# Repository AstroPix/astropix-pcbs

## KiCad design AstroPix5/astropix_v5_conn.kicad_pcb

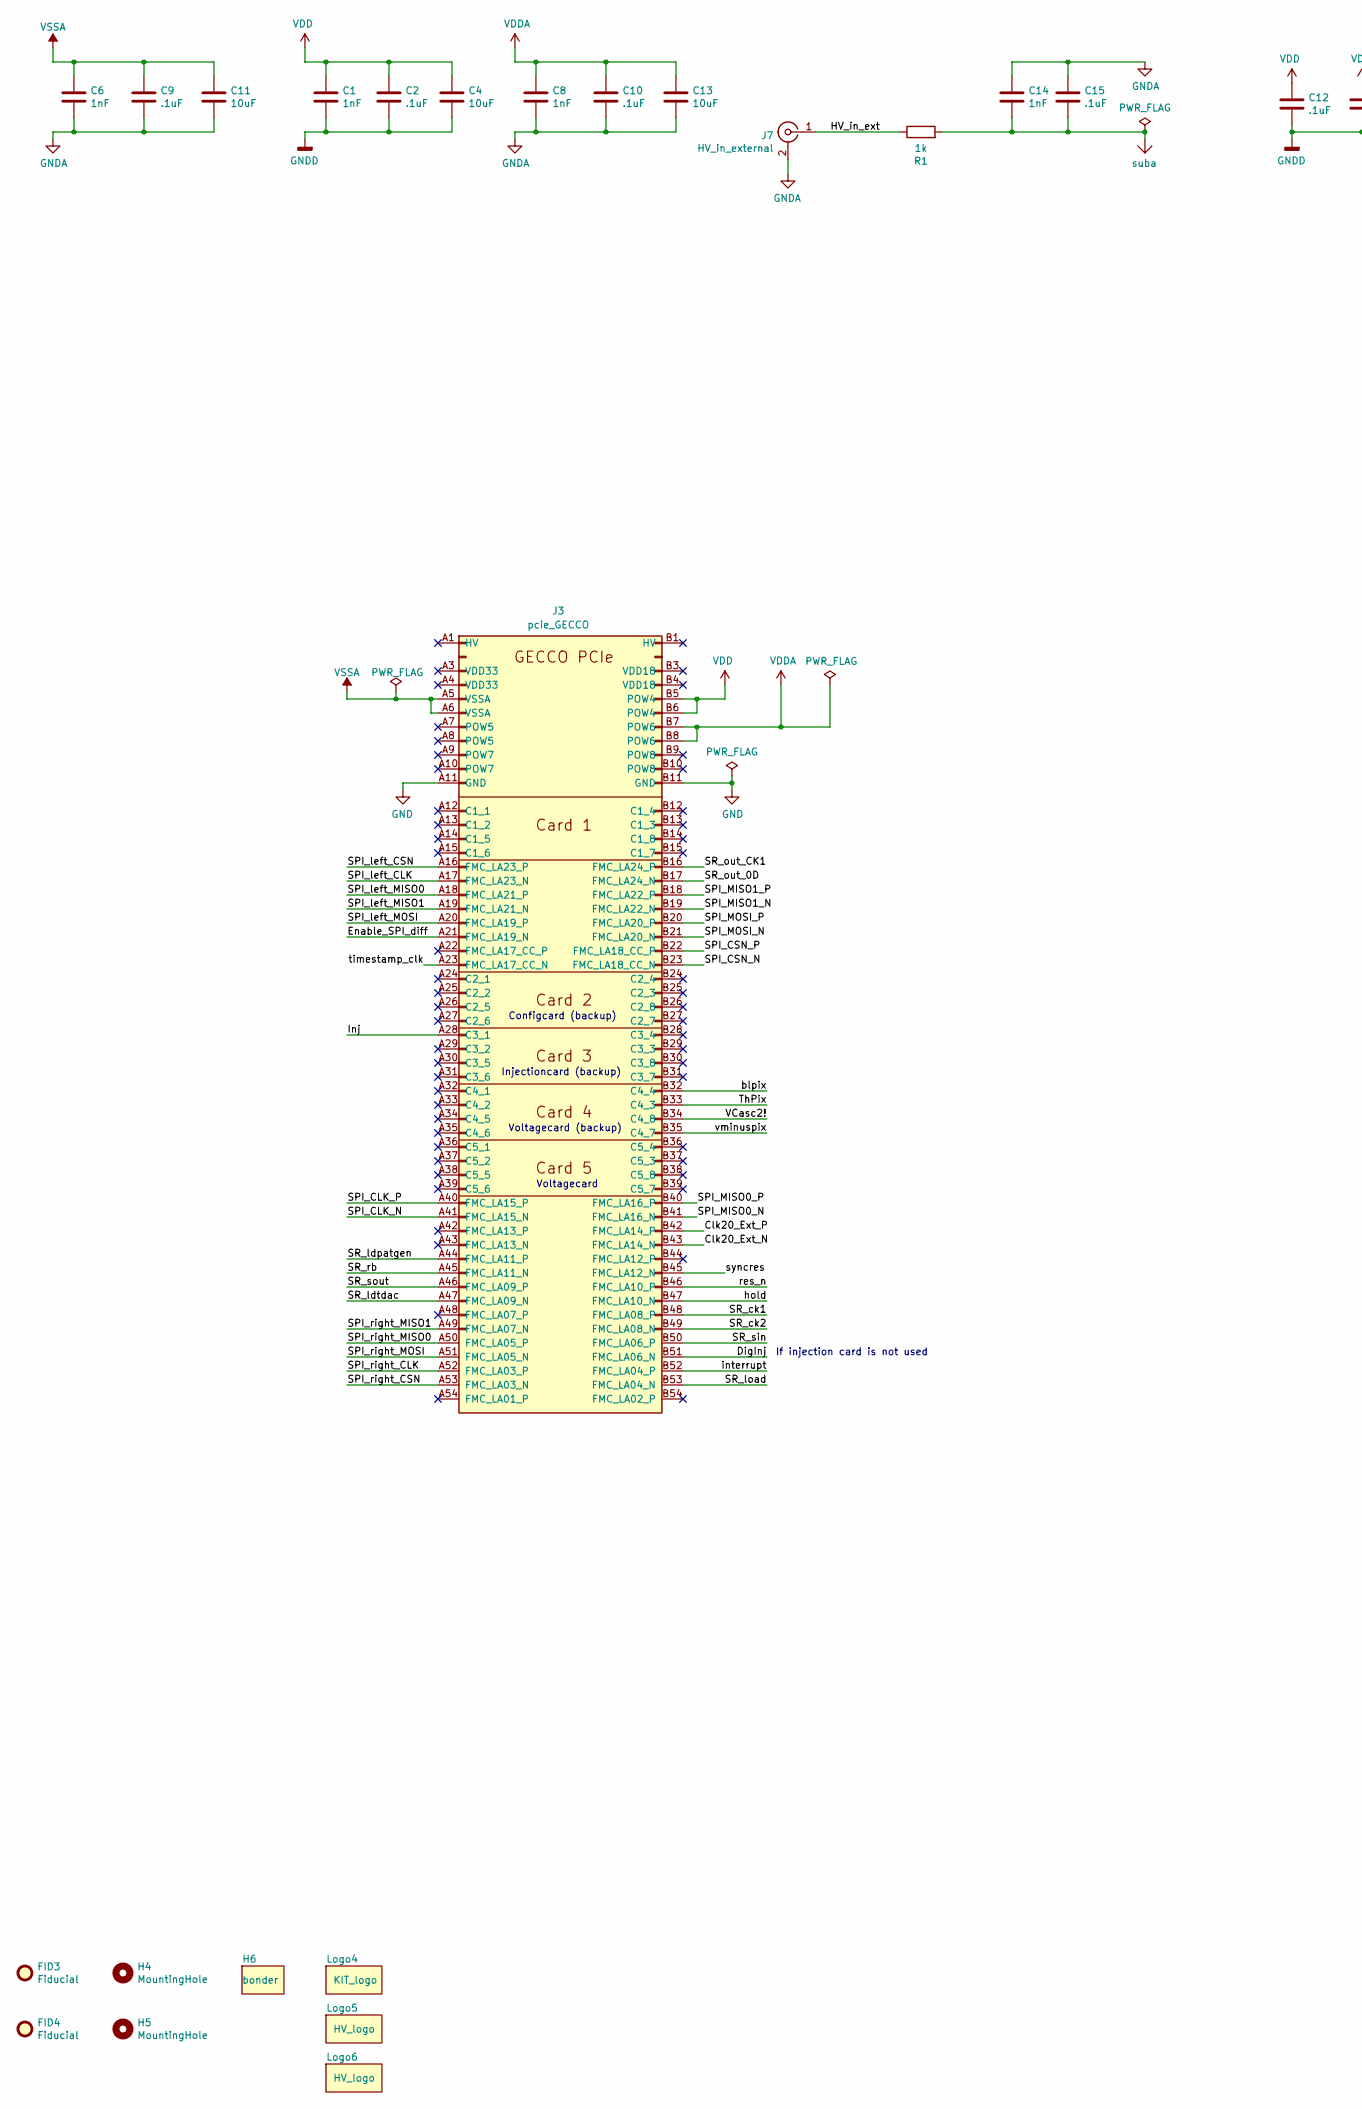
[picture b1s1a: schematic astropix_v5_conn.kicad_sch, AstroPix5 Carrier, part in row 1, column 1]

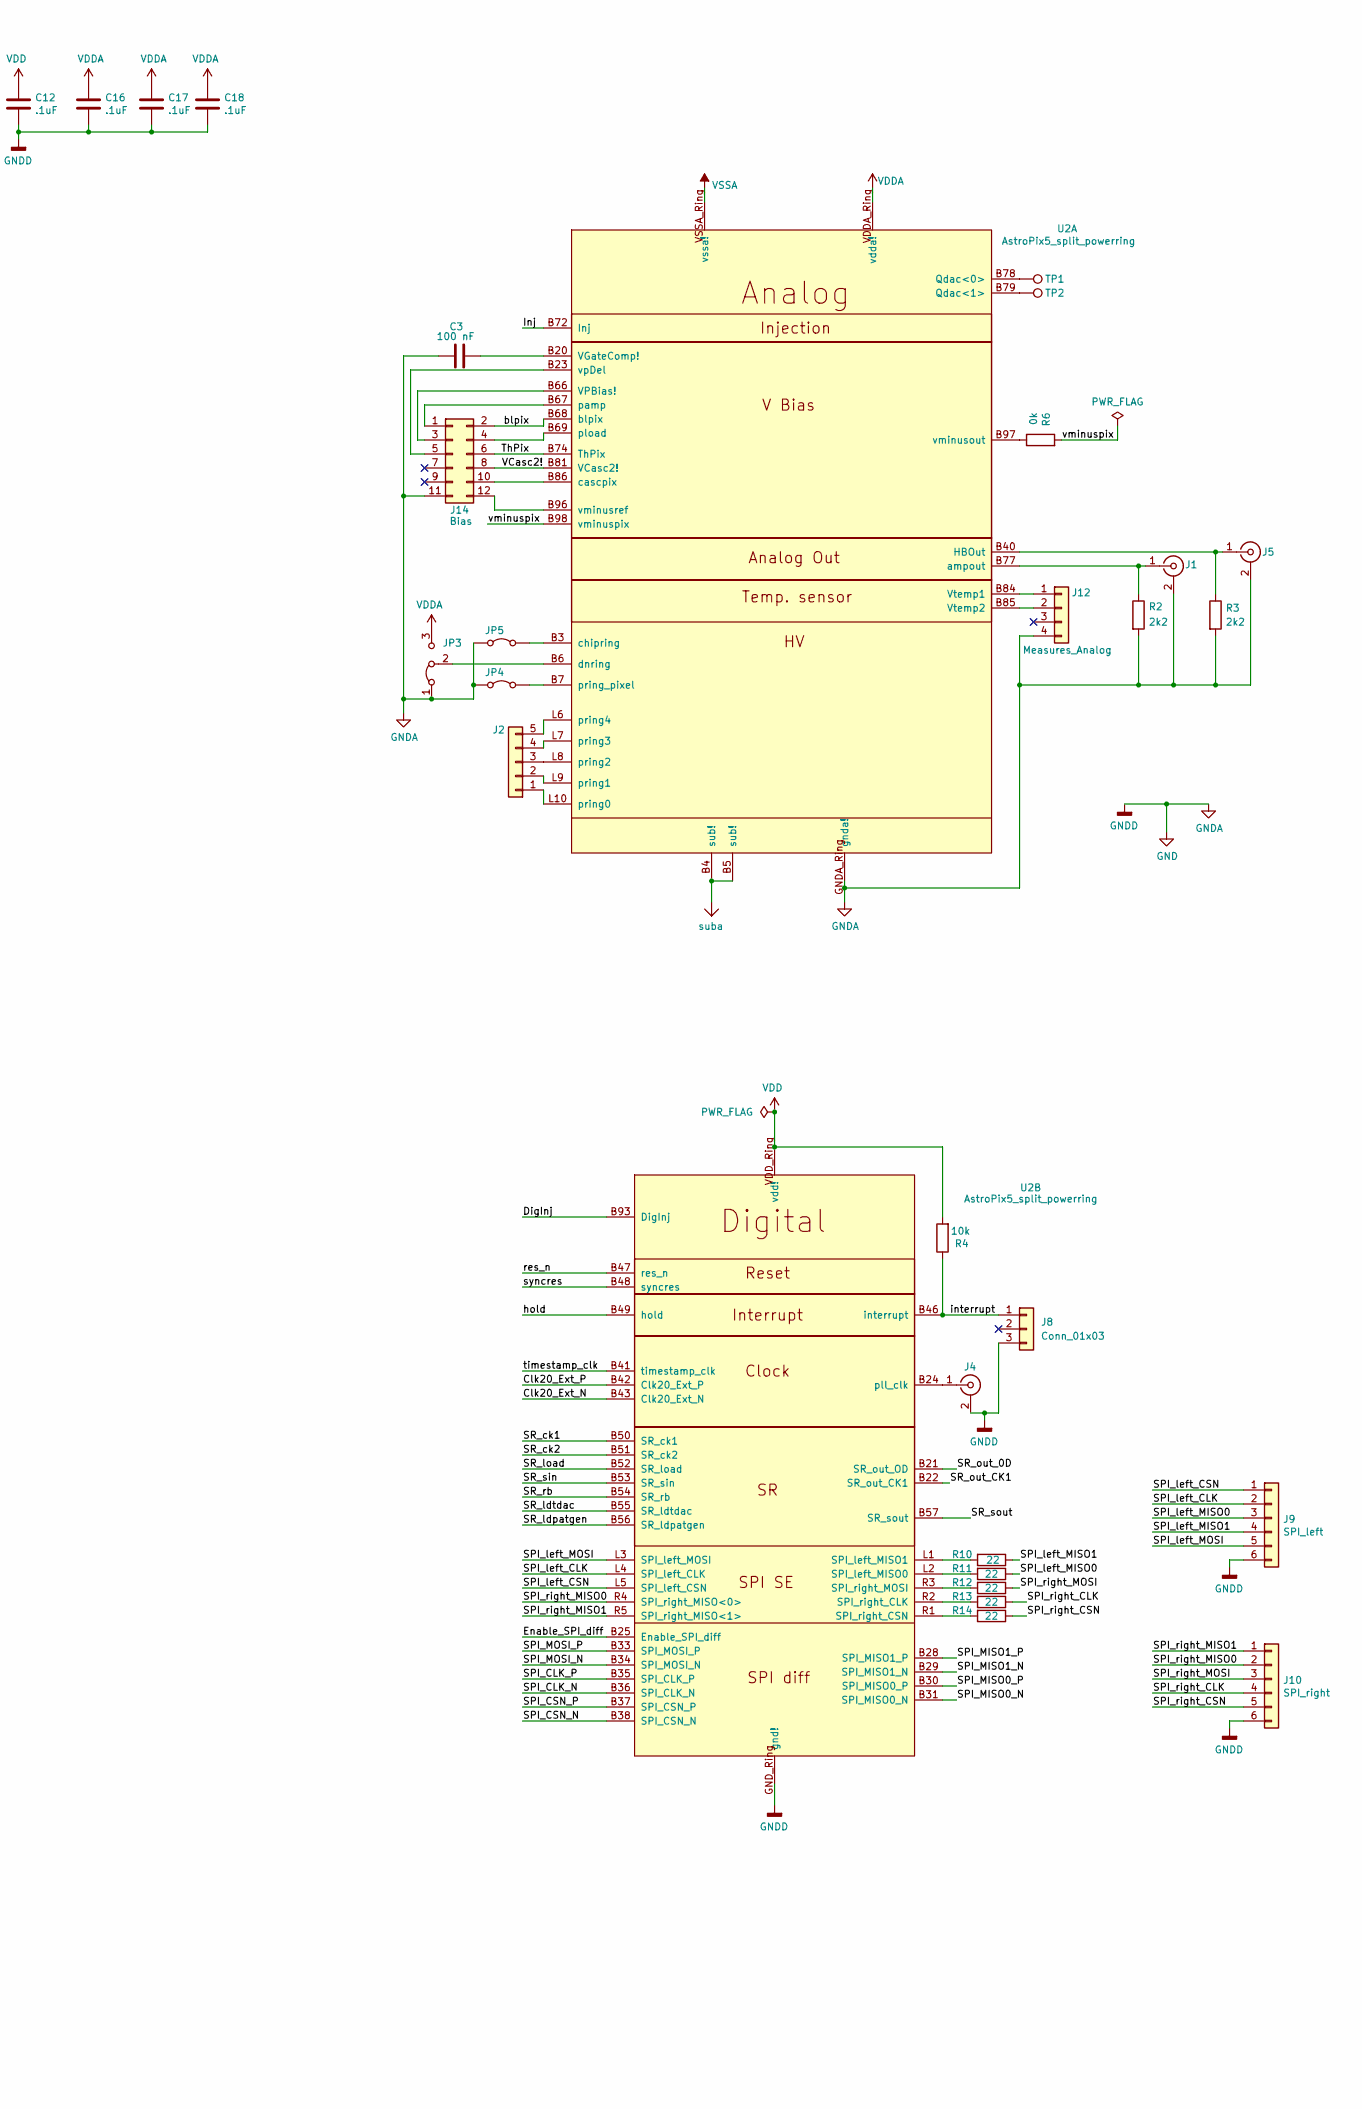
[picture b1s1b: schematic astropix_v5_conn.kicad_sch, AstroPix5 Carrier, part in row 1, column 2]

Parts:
C1, C6, C8: 1nF; C_0603_1608Metric; Tolerance 10%
C2, C9, C10, C12, C16, C17, C18: .1uF; C_0603_1608Metric; Tolerance 10%
C3: 100 nF; C_0603_1608Metric; Tolerance 10%
C4, C11, C13: 10uF; C_0603_1608Metric; Tolerance 10%
C14: 1nF; C_1210_3225Metric; Voltage 500V; Tolerance 10%
C15: .1uF; C_1210_3225Metric; Voltage 500V; Tolerance 10%
FID3, FID4: Fiducial; Fiducial_1mm_Mask2mm
H4, H5: MountingHole; MountingHole_3.2mm_M3
H6: bonder
J1, J4, J5: HBOut; SMA_Molex_73251-2200_Horizontal
J2: Conn_01x05; PinHeader_1x05_P2.54mm_Vertical
J3: pcie_GECCO; BUS_PCIexpress_x16_ilo
J7: HV_in_external; SMA_Molex_73251-2200_Horizontal
J8: Conn_01x03; PinHeader_1x03_P2.54mm_Vertical
J9: SPI_left; PinHeader_1x06_P2.54mm_Vertical
J10: SPI_right; PinHeader_1x06_P2.54mm_Vertical
J12: Measures_Analog; PinHeader_1x04_P2.54mm_Vertical
J14: Bias; PinHeader_1x12_P2.54mm_Horizontal
JP3: Jumper_3_Bridged12; PinHeader_1x03_P2.54mm_Vertical
JP4, JP5: Jumper_2_Bridged; PinHeader_1x02_P2.54mm_Vertical
Logo4: KIT_logo; logo
Logo5, Logo6: HV_logo; hv
R1: 1k; R_0603_1608Metric; Tolerance 1%
R2, R3: 2k2; R_0603_1608Metric; Tolerance 1%
R4: 10k; R_0603_1608Metric; Tolerance 1%
R6: 0k; R_0603_1608Metric; Tolerance 0Ω
R10, R11, R12, R13, R14: 22; R_0402_1005Metric; Tolerance 1%
TP1, TP2: TestPoint; TestPoint_Loop_D1.80mm_Drill1.0mm_Beaded
U2: AstroPix5_split_powerring; AstroPix5_v2

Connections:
/Clk20_Ext_N: J3.B43 (FMC_LA14_N), U2.B43 (Clk20_Ext_N)
/Clk20_Ext_P: J3.B42 (FMC_LA14_P), U2.B42 (Clk20_Ext_P)
/DigInj: J3.B51 (FMC_LA06_N), U2.B93 (DigInj)
/Enable_SPI_diff: J3.A21 (FMC_LA19_N), U2.B25 (Enable_SPI_diff)
/HV_in_ext: J7.1 (In), R1.1
/Inj: J3.A28 (C3_1), U2.B72 (Inj)
/SPI_CLK_N: J3.A41 (FMC_LA15_N), U2.B36 (SPI_CLK_N)
/SPI_CLK_P: J3.A40 (FMC_LA15_P), U2.B35 (SPI_CLK_P)
/SPI_CSN_N: J3.B23 (FMC_LA18_CC_N), U2.B38 (SPI_CSN_N)
/SPI_CSN_P: J3.B22 (FMC_LA18_CC_P), U2.B37 (SPI_CSN_P)
/SPI_MISO0_N: J3.B41 (FMC_LA16_N), U2.B31 (SPI_MISO0_N)
/SPI_MISO0_P: J3.B40 (FMC_LA16_P), U2.B30 (SPI_MISO0_P)
/SPI_MISO1_N: J3.B19 (FMC_LA22_N), U2.B29 (SPI_MISO1_N)
/SPI_MISO1_P: J3.B18 (FMC_LA22_P), U2.B28 (SPI_MISO1_P)
/SPI_MOSI_N: J3.B21 (FMC_LA20_N), U2.B34 (SPI_MOSI_N)
/SPI_MOSI_P: J3.B20 (FMC_LA20_P), U2.B33 (SPI_MOSI_P)
/SPI_left_CLK: J3.A17 (FMC_LA23_N), J9.2, U2.L4 (SPI_left_CLK)
/SPI_left_CSN: J3.A16 (FMC_LA23_P), J9.1, U2.L5 (SPI_left_CSN)
/SPI_left_MISO0: J3.A18 (FMC_LA21_P), J9.3, R11.1
/SPI_left_MISO1: J3.A19 (FMC_LA21_N), J9.4, R10.1
/SPI_left_MOSI: J3.A20 (FMC_LA19_P), J9.5, U2.L3 (SPI_left_MOSI)
/SPI_right_CLK: J3.A52 (FMC_LA03_P), J10.4, R13.1
/SPI_right_CSN: J3.A53 (FMC_LA03_N), J10.5, R14.1
/SPI_right_MISO0: J3.A50 (FMC_LA05_P), J10.2, U2.R4 (SPI_right_MISO<0>)
/SPI_right_MISO1: J3.A49 (FMC_LA07_N), J10.1, U2.R5 (SPI_right_MISO<1>)
/SPI_right_MOSI: J3.A51 (FMC_LA05_N), J10.3, R12.1
/SR_ck1: J3.B48 (FMC_LA08_P), U2.B50 (SR_ck1)
/SR_ck2: J3.B49 (FMC_LA08_N), U2.B51 (SR_ck2)
/SR_ldpatgen: J3.A44 (FMC_LA11_P), U2.B56 (SR_ldpatgen)
/SR_ldtdac: J3.A47 (FMC_LA09_N), U2.B55 (SR_ldtdac)
/SR_load: J3.B53 (FMC_LA04_N), U2.B52 (SR_load)
/SR_out_0D: J3.B17 (FMC_LA24_N), U2.B21 (SR_out_OD)
/SR_out_CK1: J3.B16 (FMC_LA24_P), U2.B22 (SR_out_CK1)
/SR_rb: J3.A45 (FMC_LA11_N), U2.B54 (SR_rb)
/SR_sin: J3.B50 (FMC_LA06_P), U2.B53 (SR_sin)
/SR_sout: J3.A46 (FMC_LA09_P), U2.B57 (SR_sout)
/ThPix: J3.B33 (C4_3), J14.6, U2.B74 (ThPix)
/VCasc2!: J3.B34 (C4_8), J14.8, U2.B81 (VCasc2!)
/blpix: J3.B32 (C4_4), J14.2, U2.B68 (blpix)
/hold: J3.B47 (FMC_LA10_N), U2.B49 (hold)
/interrupt: J3.B52 (FMC_LA04_P), J8.1, R4.1, U2.B46 (interrupt)
/res_n: J3.B46 (FMC_LA10_P), U2.B47 (res_n)
/syncres: J3.B45 (FMC_LA12_N), U2.B48 (syncres)
/timestamp_clk: J3.A23 (FMC_LA17_CC_N), U2.B41 (timestamp_clk)
/vminuspix: J3.B35 (C4_7), R6.2, U2.B98 (vminuspix)
GND: C1.2, C2.2, C3.1, C4.2, C6.2, C8.2, C9.2, C10.2, C11.2, C12.2, C13.2, C14.1, C15.1, C16.2, C17.2, C18.2, J1.2 (Ext), J3.A11 (GND), J3.B11 (GND), J4.2 (Ext), J5.2 (Ext), J7.2 (Ext), J8.3, J9.6, J10.6, J12.4, J14.11, JP3.1 (A), JP4.1 (A), JP5.1 (A), R2.2, R3.2, U2.GNDA_Ring (gnda!), U2.GND_Ring (gnd!)
unnamed: J1.1 (In), R2.1, U2.B77 (ampout)
unnamed: J2.1, U2.L10 (pring0)
unnamed: J2.2, U2.L9 (pring1)
unnamed: J2.3, U2.L8 (pring2)
unnamed: J2.4, U2.L7 (pring3)
unnamed: J2.5, U2.L6 (pring4)
unnamed: J4.1 (In), U2.B24 (pll_clk)
unnamed: J5.1 (In), R3.1, U2.B40 (HBOut)
unnamed: J12.1, U2.B84 (Vtemp1)
unnamed: J12.2, U2.B85 (Vtemp2)
unnamed: J14.1, U2.B67 (pamp)
unnamed: J14.3, U2.B66 (VPBias!)
unnamed: J14.4, U2.B69 (pload)
unnamed: J14.5, U2.B23 (vpDel)
unnamed: J14.10, U2.B86 (cascpix)
unnamed: J14.12, U2.B96 (vminusref)
unnamed: JP3.2 (C), U2.B6 (dnring)
unnamed: JP4.2 (B), U2.B7 (pring_pixel)
unnamed: JP5.2 (B), U2.B3 (chipring)
unnamed: TP1.1 (1_1), U2.B78 (Qdac<0>)
unnamed: TP2.1 (1_1), U2.B79 (Qdac<1>)
unnamed: C3.2, U2.B20 (VGateComp!)
unnamed: R6.1, U2.B97 (vminusout)
unnamed: R11.2, U2.L2 (SPI_left_MISO0)
unnamed: R10.2, U2.L1 (SPI_left_MISO1)
unnamed: R13.2, U2.R2 (SPI_right_CLK)
unnamed: R14.2, U2.R1 (SPI_right_CSN)
unnamed: R12.2, U2.R3 (SPI_right_MOSI)
VDD: C1.1, C2.1, C4.1, C12.1, J3.B5 (POW4), J3.B6 (POW4), R4.2, U2.VDD_Ring (vdd!)
VDDA: C8.1, C10.1, C13.1, C16.1, C17.1, C18.1, J3.B7 (POW6), J3.B8 (POW6), JP3.3 (B), U2.VDDA_Ring (vdda!)
VSSA: C6.1, C9.1, C11.1, J3.A5 (VSSA), J3.A6 (VSSA), U2.VSSA_Ring (vssa!)
suba: C14.2, C15.2, R1.2, U2.B4 (sub!), U2.B5 (sub!)

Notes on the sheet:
If injection card is not used
Injectioncard (backup)
Voltagecard (backup)
Voltagecard
Configcard (backup)

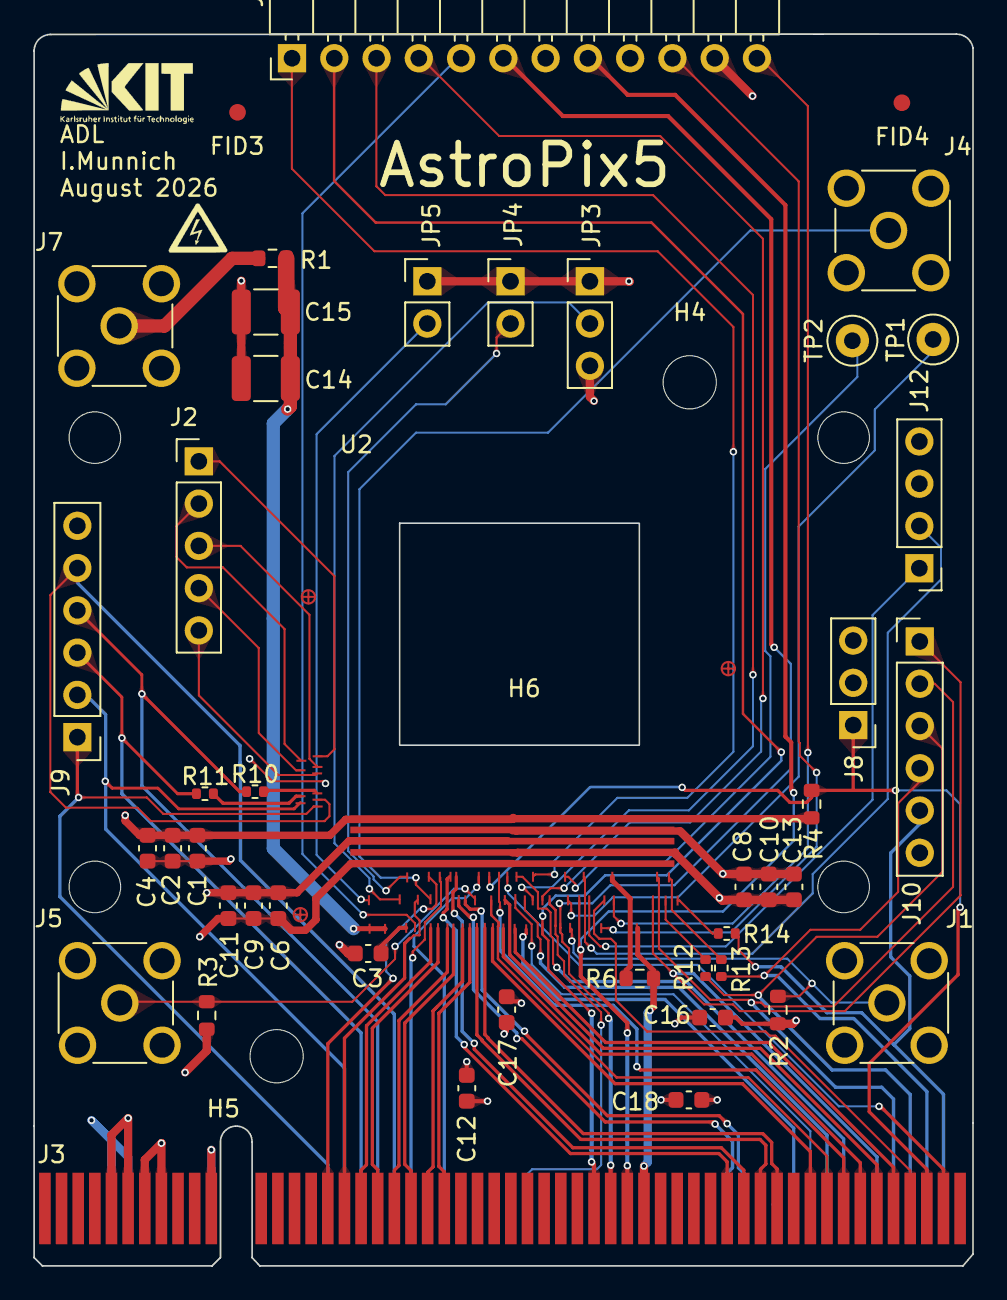
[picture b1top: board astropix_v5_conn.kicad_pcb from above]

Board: 4 copper layers, 56.4 x 74.0 mm, 50 parts (0 on the bottom side), 78 nets.
